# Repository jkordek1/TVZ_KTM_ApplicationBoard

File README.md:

# TVZ_KTM_ApplicationBoard

Expansion board for two Nucleo 64 boards (master and slave), developed in 2022 for students studying at Zagreb university of applied sciences.
It enables quick and easy firmware development without the need of connecting different modules via breadboard and jumpers.

## Images

 ## Features
 - Toggle switches
 - LEDs
 - MCP2551 high-speed CAN transceiver
 - Digital I2C temperature sensor with address selection jumpers
 - UART, CAN, Parallel, analog, SPI and I2C communications between master and slave
 - Probe clips for easy oscilloscope connections
 
 ## Folder structure
    .
    ├── ...
    ├── 3d models               # 3D models of components
    ├── Images                  # Images of the project
    ├── KiCAD files             # Main KiCAD project folder
    │   ├── Datasheet           # Datasheet collection
    │   ├── jlcpcb              # jlcpcb production files
    │   ├── Graphics            # Custom graphics for PCB
    │   └── gerber              # gerber output folder
    └── ...

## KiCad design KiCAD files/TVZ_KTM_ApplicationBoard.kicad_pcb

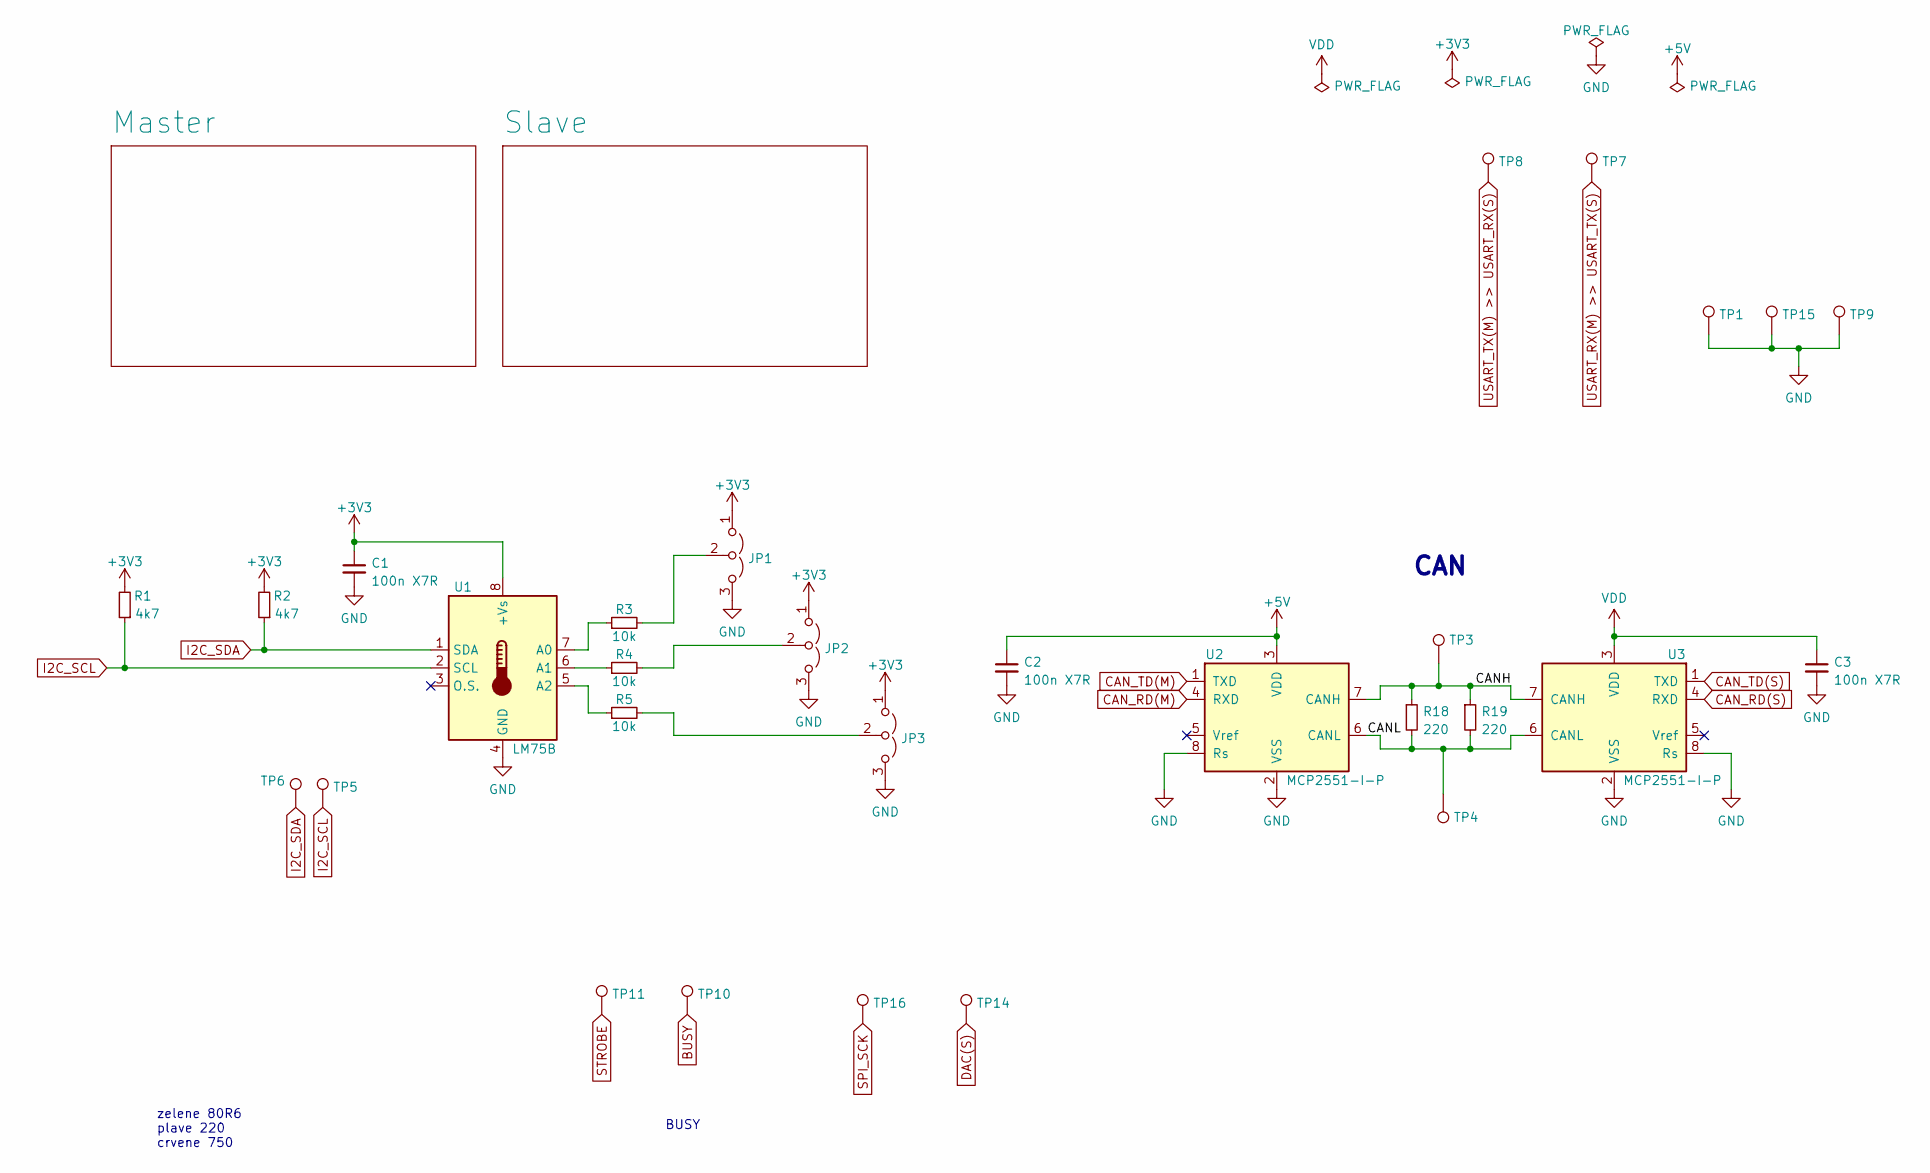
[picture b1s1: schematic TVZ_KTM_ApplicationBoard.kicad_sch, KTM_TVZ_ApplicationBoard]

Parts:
C1, C2, C3: 100n X7R; C_0805_2012Metric
JP1, JP2, JP3: Jumper_3_Open; PinHeader_1x03_P2.54mm_Vertical
R1, R2: 4k7; R_0805_2012Metric
R3, R4, R5: 10k; R_0805_2012Metric
R18, R19: 220; R_0805_2012Metric
TP1, TP3, TP4, TP5, TP6, TP7, TP8, TP9, TP10, TP11, TP14, TP15, TP16: TestPoint; KEYS4952
U1: LM75B; SO-8_3.9x4.9mm_P1.27mm
U2, U3: MCP2551-I-P; DIP-8_W7.62mm

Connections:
+3V3: C1.1, JP1.1 (A), JP2.1 (A), JP3.1 (A), R1.2, R2.2, U1.8 (+Vs); also elsewhere on the board
+5V: C2.1, U2.3 (VDD); also elsewhere on the board
/CANH: R18.1, R19.1, TP3.1, U2.7 (CANH), U3.7 (CANH)
/CANL: R18.2, R19.2, TP4.1, U2.6 (CANL), U3.6 (CANL)
BUSY: TP10.1; also elsewhere on the board
CAN_RD(M): U2.4 (RXD); also elsewhere on the board
CAN_RD(S): U3.4 (RXD); also elsewhere on the board
CAN_TD(M): U2.1 (TXD); also elsewhere on the board
CAN_TD(S): U3.1 (TXD); also elsewhere on the board
DAC(S): TP14.1; also elsewhere on the board
GND: C1.2, C2.2, C3.2, JP1.3 (B), JP2.3 (B), JP3.3 (B), TP1.1, TP9.1, TP15.1, U1.4 (GND), U2.2 (VSS), U2.8 (Rs), U3.2 (VSS), U3.8 (Rs); also elsewhere on the board
I2C_SCL: R1.1, TP5.1, U1.2 (SCL); also elsewhere on the board
I2C_SDA: R2.1, TP6.1, U1.1 (SDA); also elsewhere on the board
unnamed: JP1.2 (C), R3.2
unnamed: JP2.2 (C), R4.2
unnamed: JP3.2 (C), R5.2
unnamed: R3.1, U1.7 (A0)
unnamed: R4.1, U1.6 (A1)
unnamed: R5.1, U1.5 (A2)
SPI_SCK: TP16.1; also elsewhere on the board
STROBE: TP11.1; also elsewhere on the board
USART_RX(M) >> USART_TX(S): TP7.1; also elsewhere on the board
USART_TX(M) >> USART_RX(S): TP8.1; also elsewhere on the board
VDD: C3.1, U3.3 (VDD); also elsewhere on the board

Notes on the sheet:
CAN
BUSY
zelene 80R6 plave 220 crvene 750

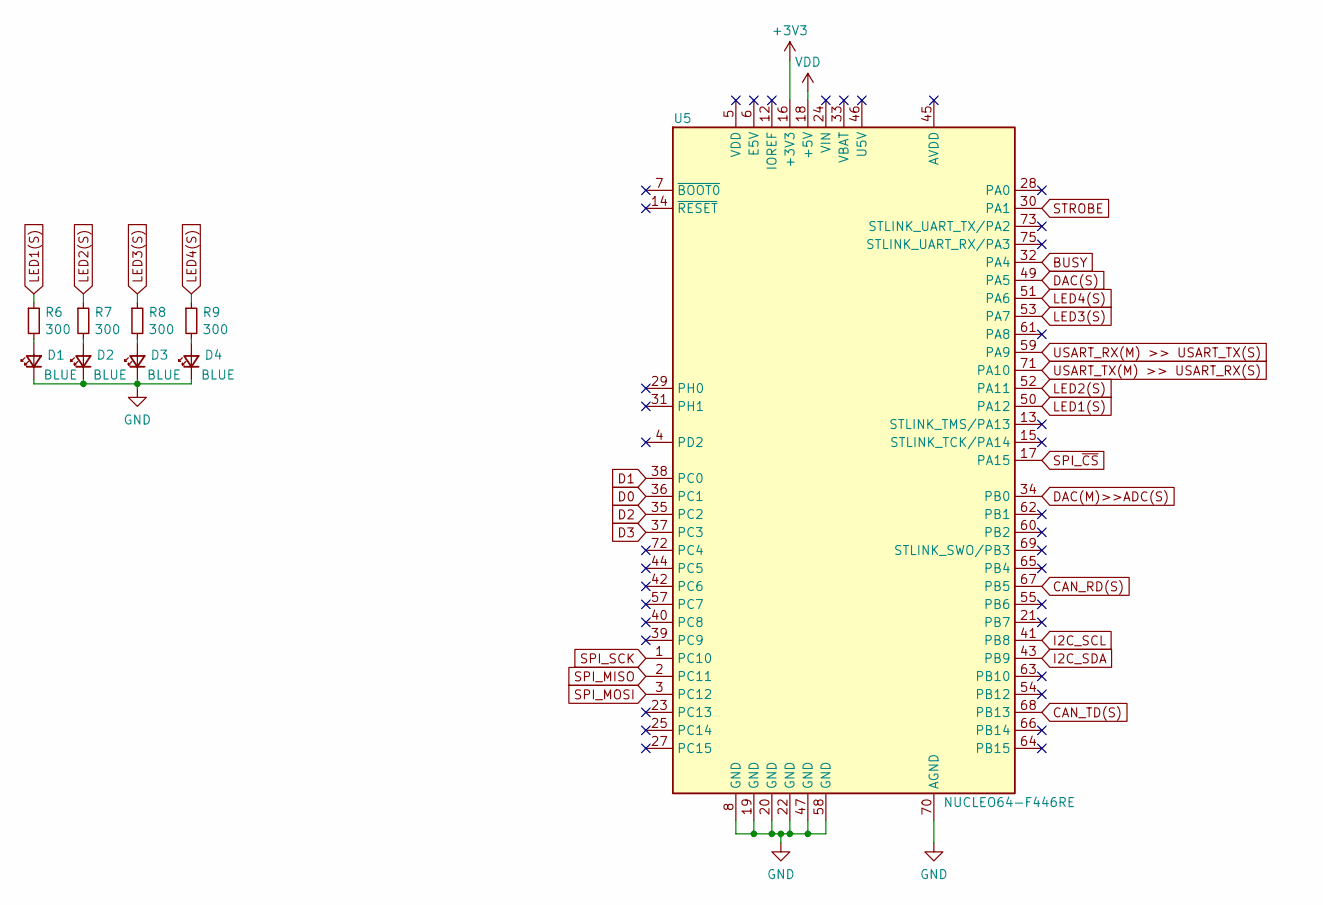
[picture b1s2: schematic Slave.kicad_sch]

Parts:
D1, D2, D3, D4: BLUE; LED_1206_3216Metric
R6, R7, R8, R9: 300; R_0805_2012Metric
U5: NUCLEO64-F446RE; NUCLEO64

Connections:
+3V3: U5.16 (+3V3); also elsewhere on the board
BUSY: U5.32 (PA4); also elsewhere on the board
CAN_RD(S): U5.67 (PB5); also elsewhere on the board
CAN_TD(S): U5.68 (PB13); also elsewhere on the board
D0: U5.36 (PC1); also elsewhere on the board
D1: U5.38 (PC0); also elsewhere on the board
D2: U5.35 (PC2); also elsewhere on the board
D3: U5.37 (PC3); also elsewhere on the board
DAC(M)>>ADC(S): U5.34 (PB0); also elsewhere on the board
DAC(S): U5.49 (PA5); also elsewhere on the board
GND: D1.1 (K), D2.1 (K), D3.1 (K), D4.1 (K), U5.8 (GND), U5.19 (GND), U5.20 (GND), U5.22 (GND), U5.47 (GND), U5.58 (GND), U5.70 (AGND); also elsewhere on the board
I2C_SCL: U5.41 (PB8); also elsewhere on the board
I2C_SDA: U5.43 (PB9); also elsewhere on the board
LED1(S): R6.1, U5.50 (PA12)
LED2(S): R7.1, U5.52 (PA11)
LED3(S): R8.1, U5.53 (PA7)
LED4(S): R9.1, U5.51 (PA6)
unnamed: D1.2 (A), R6.2
unnamed: D2.2 (A), R7.2
unnamed: D3.2 (A), R8.2
unnamed: D4.2 (A), R9.2
SPI_MISO: U5.2 (PC11); also elsewhere on the board
SPI_MOSI: U5.3 (PC12); also elsewhere on the board
SPI_SCK: U5.1 (PC10); also elsewhere on the board
SPI_~CS: U5.17 (PA15); also elsewhere on the board
STROBE: U5.30 (PA1); also elsewhere on the board
USART_RX(M) >> USART_TX(S): U5.59 (PA9); also elsewhere on the board
USART_TX(M) >> USART_RX(S): U5.71 (PA10); also elsewhere on the board
VDD: U5.18 (+5V); also elsewhere on the board

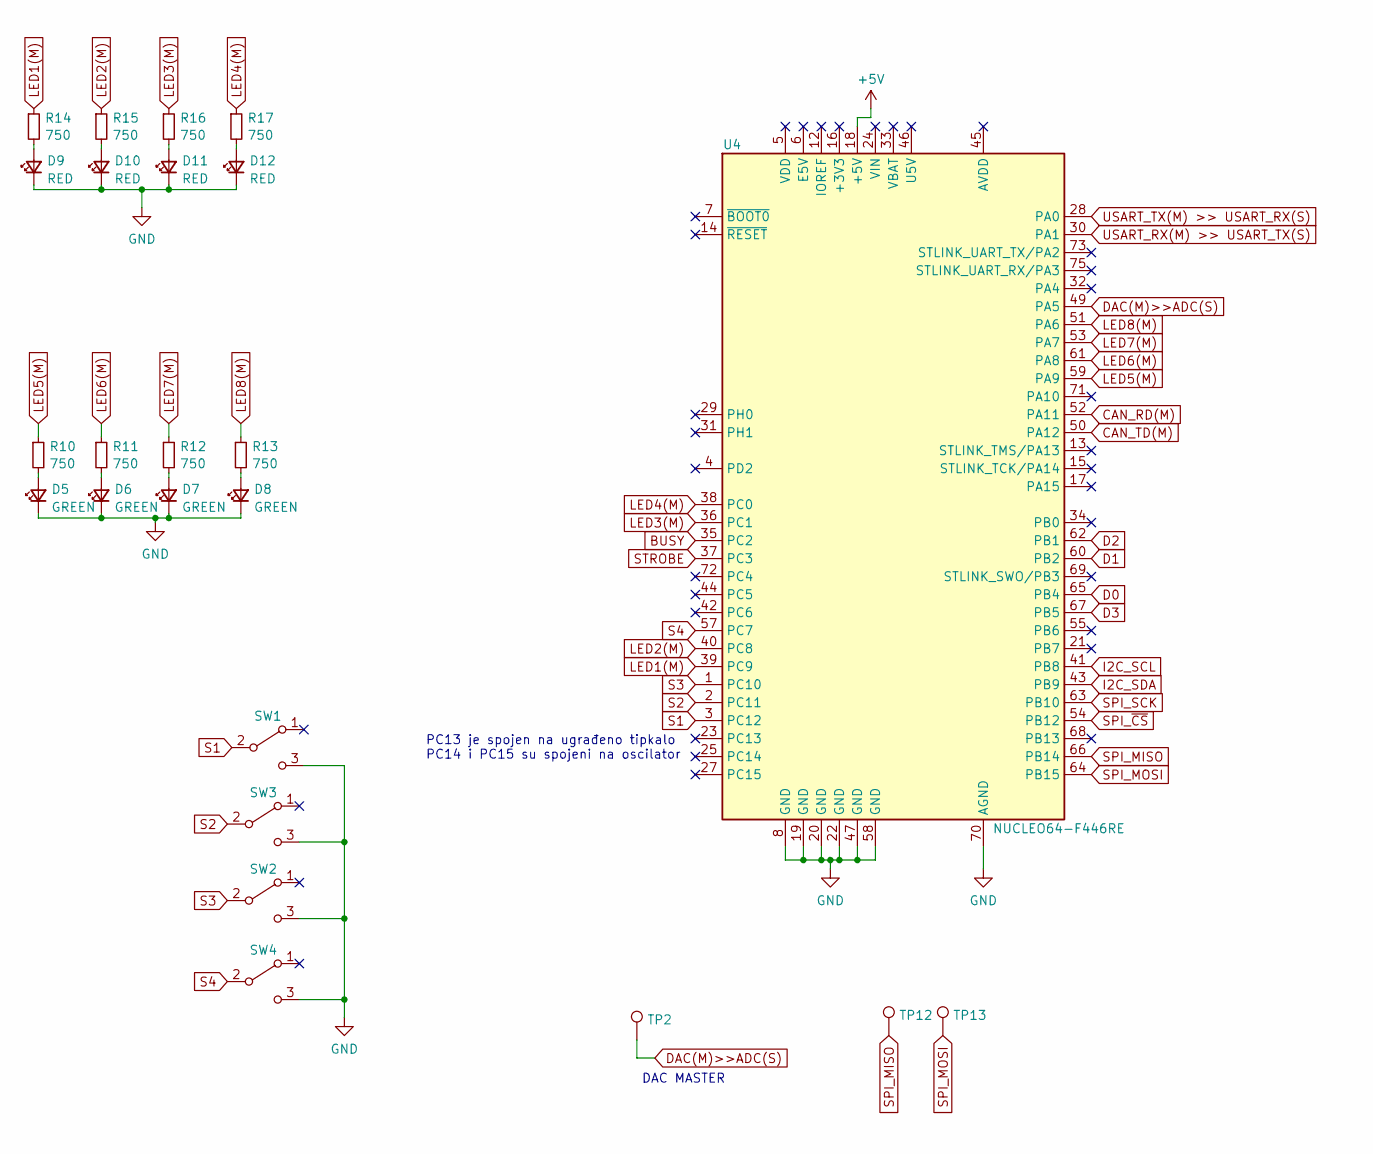
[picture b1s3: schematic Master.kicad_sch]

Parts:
D5, D6, D7, D8: GREEN; LED_1206_3216Metric
D9, D10, D11, D12: RED; LED_1206_3216Metric
R10, R11, R12, R13, R14, R15, R16, R17: 750; R_0805_2012Metric
SW1, SW2, SW3, SW4: EG1271A
TP2, TP12, TP13: TestPoint; KEYS4952
U4: NUCLEO64-F446RE; NUCLEO64

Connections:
+5V: U4.18 (+5V); also elsewhere on the board
BUSY: U4.35 (PC2); also elsewhere on the board
CAN_RD(M): U4.52 (PA11); also elsewhere on the board
CAN_TD(M): U4.50 (PA12); also elsewhere on the board
D0: U4.65 (PB4); also elsewhere on the board
D1: U4.60 (PB2); also elsewhere on the board
D2: U4.62 (PB1); also elsewhere on the board
D3: U4.67 (PB5); also elsewhere on the board
DAC(M)>>ADC(S): TP2.1, U4.49 (PA5); also elsewhere on the board
GND: D5.1 (K), D6.1 (K), D7.1 (K), D8.1 (K), D9.1 (K), D10.1 (K), D11.1 (K), D12.1 (K), SW1.3 (C), SW2.3 (C), SW3.3 (C), SW4.3 (C), U4.8 (GND), U4.19 (GND), U4.20 (GND), U4.22 (GND), U4.47 (GND), U4.58 (GND), U4.70 (AGND); also elsewhere on the board
I2C_SCL: U4.41 (PB8); also elsewhere on the board
I2C_SDA: U4.43 (PB9); also elsewhere on the board
LED1(M): R14.1, U4.39 (PC9)
LED2(M): R15.1, U4.40 (PC8)
LED3(M): R16.1, U4.36 (PC1)
LED4(M): R17.1, U4.38 (PC0)
LED5(M): R10.1, U4.59 (PA9)
LED6(M): R11.1, U4.61 (PA8)
LED7(M): R12.1, U4.53 (PA7)
LED8(M): R13.1, U4.51 (PA6)
unnamed: D5.2 (A), R10.2
unnamed: D6.2 (A), R11.2
unnamed: D7.2 (A), R12.2
unnamed: D8.2 (A), R13.2
unnamed: D9.2 (A), R14.2
unnamed: D10.2 (A), R15.2
unnamed: D11.2 (A), R16.2
unnamed: D12.2 (A), R17.2
S1: SW1.2 (B), U4.3 (PC12)
S4: SW4.2 (B), U4.57 (PC7)
SPI_MISO: TP12.1, U4.66 (PB14); also elsewhere on the board
SPI_MOSI: TP13.1, U4.64 (PB15); also elsewhere on the board
SPI_SCK: U4.63 (PB10); also elsewhere on the board
SPI_~CS: U4.54 (PB12); also elsewhere on the board
STROBE: U4.37 (PC3); also elsewhere on the board
USART_RX(M) >> USART_TX(S): U4.30 (PA1); also elsewhere on the board
USART_TX(M) >> USART_RX(S): U4.28 (PA0); also elsewhere on the board

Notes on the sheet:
DAC MASTER
PC13 je spojen na ugrađeno tipkalo PC14 i PC15 su spojeni na oscilator

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
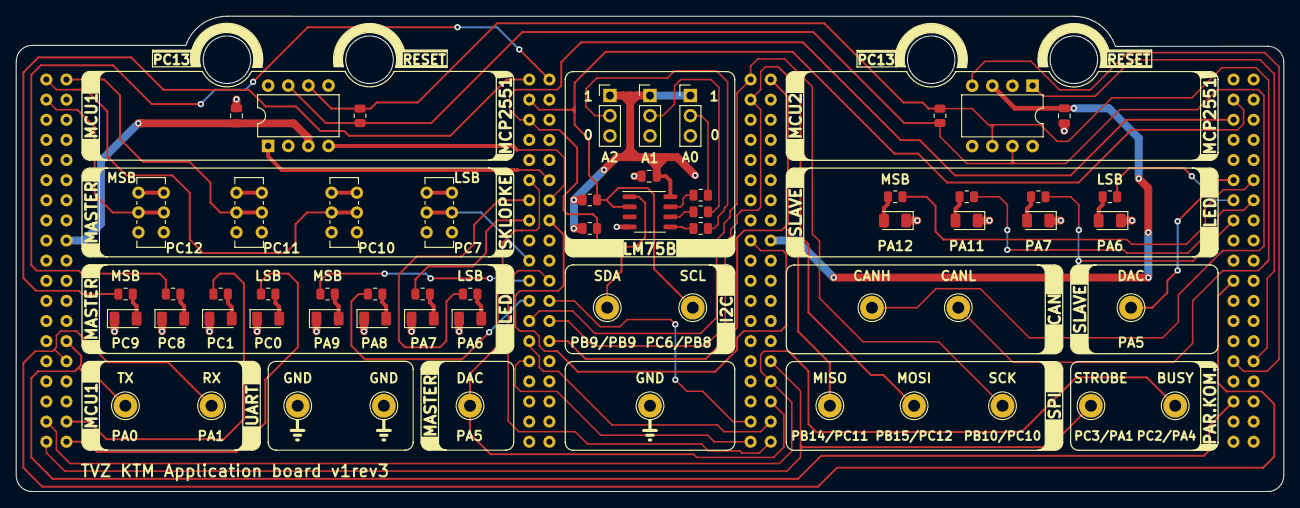
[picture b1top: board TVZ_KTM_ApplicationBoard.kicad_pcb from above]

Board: 2 copper layers, 160.0 x 60.0 mm, 62 parts (0 on the bottom side), 60 nets.

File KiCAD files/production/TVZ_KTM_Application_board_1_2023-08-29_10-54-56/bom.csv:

Designator,Footprint,Quantity,Value,LCSC Part #
"C1, C2, C3",0805,3,100n X7R,
"D1, D13, D2, D3, D4",1206,5,BLUE,
"D10, D11, D12, D9",1206,4,RED,
"D5, D6, D7, D8",1206,4,GREEN,
"JP1, JP2, JP3",PinHeader_1x03_P2.54mm_Vertical,3,Jumper_3_Open,
"R1, R2",0805,2,4k7,
"R10, R11, R12, R13, R14, R15, R16, R17",0805,8,750,
"R18, R19",0805,2,220,
"R20, R6, R7, R8, R9",0805,5,300,
"R3, R4, R5",0805,3,10k,
"SW1, SW2, SW3, SW4",EG1271A,4,EG1271A,
"TP1, TP10, TP11, TP12, TP13, TP14, TP15, TP2, TP3, TP4, TP5, TP6, TP7, TP8, TP9",KEYS4952,15,TestPoint,
U1,SO-8_3.9x4.9mm_P1.27mm,1,LM75B,
"U2, U3",DIP-8_W7.62mm,2,MCP2551-I-P,
"U4, U5",NUCLEO64,2,NUCLEO64-F446RE,

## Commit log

2022-10-24 Project created
2023-08-02 v1rev1
2023-09-29 v1rev3
